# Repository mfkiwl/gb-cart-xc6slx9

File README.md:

# Various gameboy cart projects

References:
* [ESP32 DEVKIT V4 Schematic](https://dl.espressif.com/dl/schematics/esp32_devkitc_v4-sch.pdf)
* [CMOD S6 Schematic](https://reference.digilentinc.com/_media/cmod_s6:cmods6_sch.pdf)
* [ESP32 SD Card](https://github.com/espressif/arduino-esp32/tree/master/libraries/SD)
* [ESP32 PMOD](https://reference.digilentinc.com/_media/reference/pmod/pmodesp32/schematic/pmodesp32_sch.pdf)

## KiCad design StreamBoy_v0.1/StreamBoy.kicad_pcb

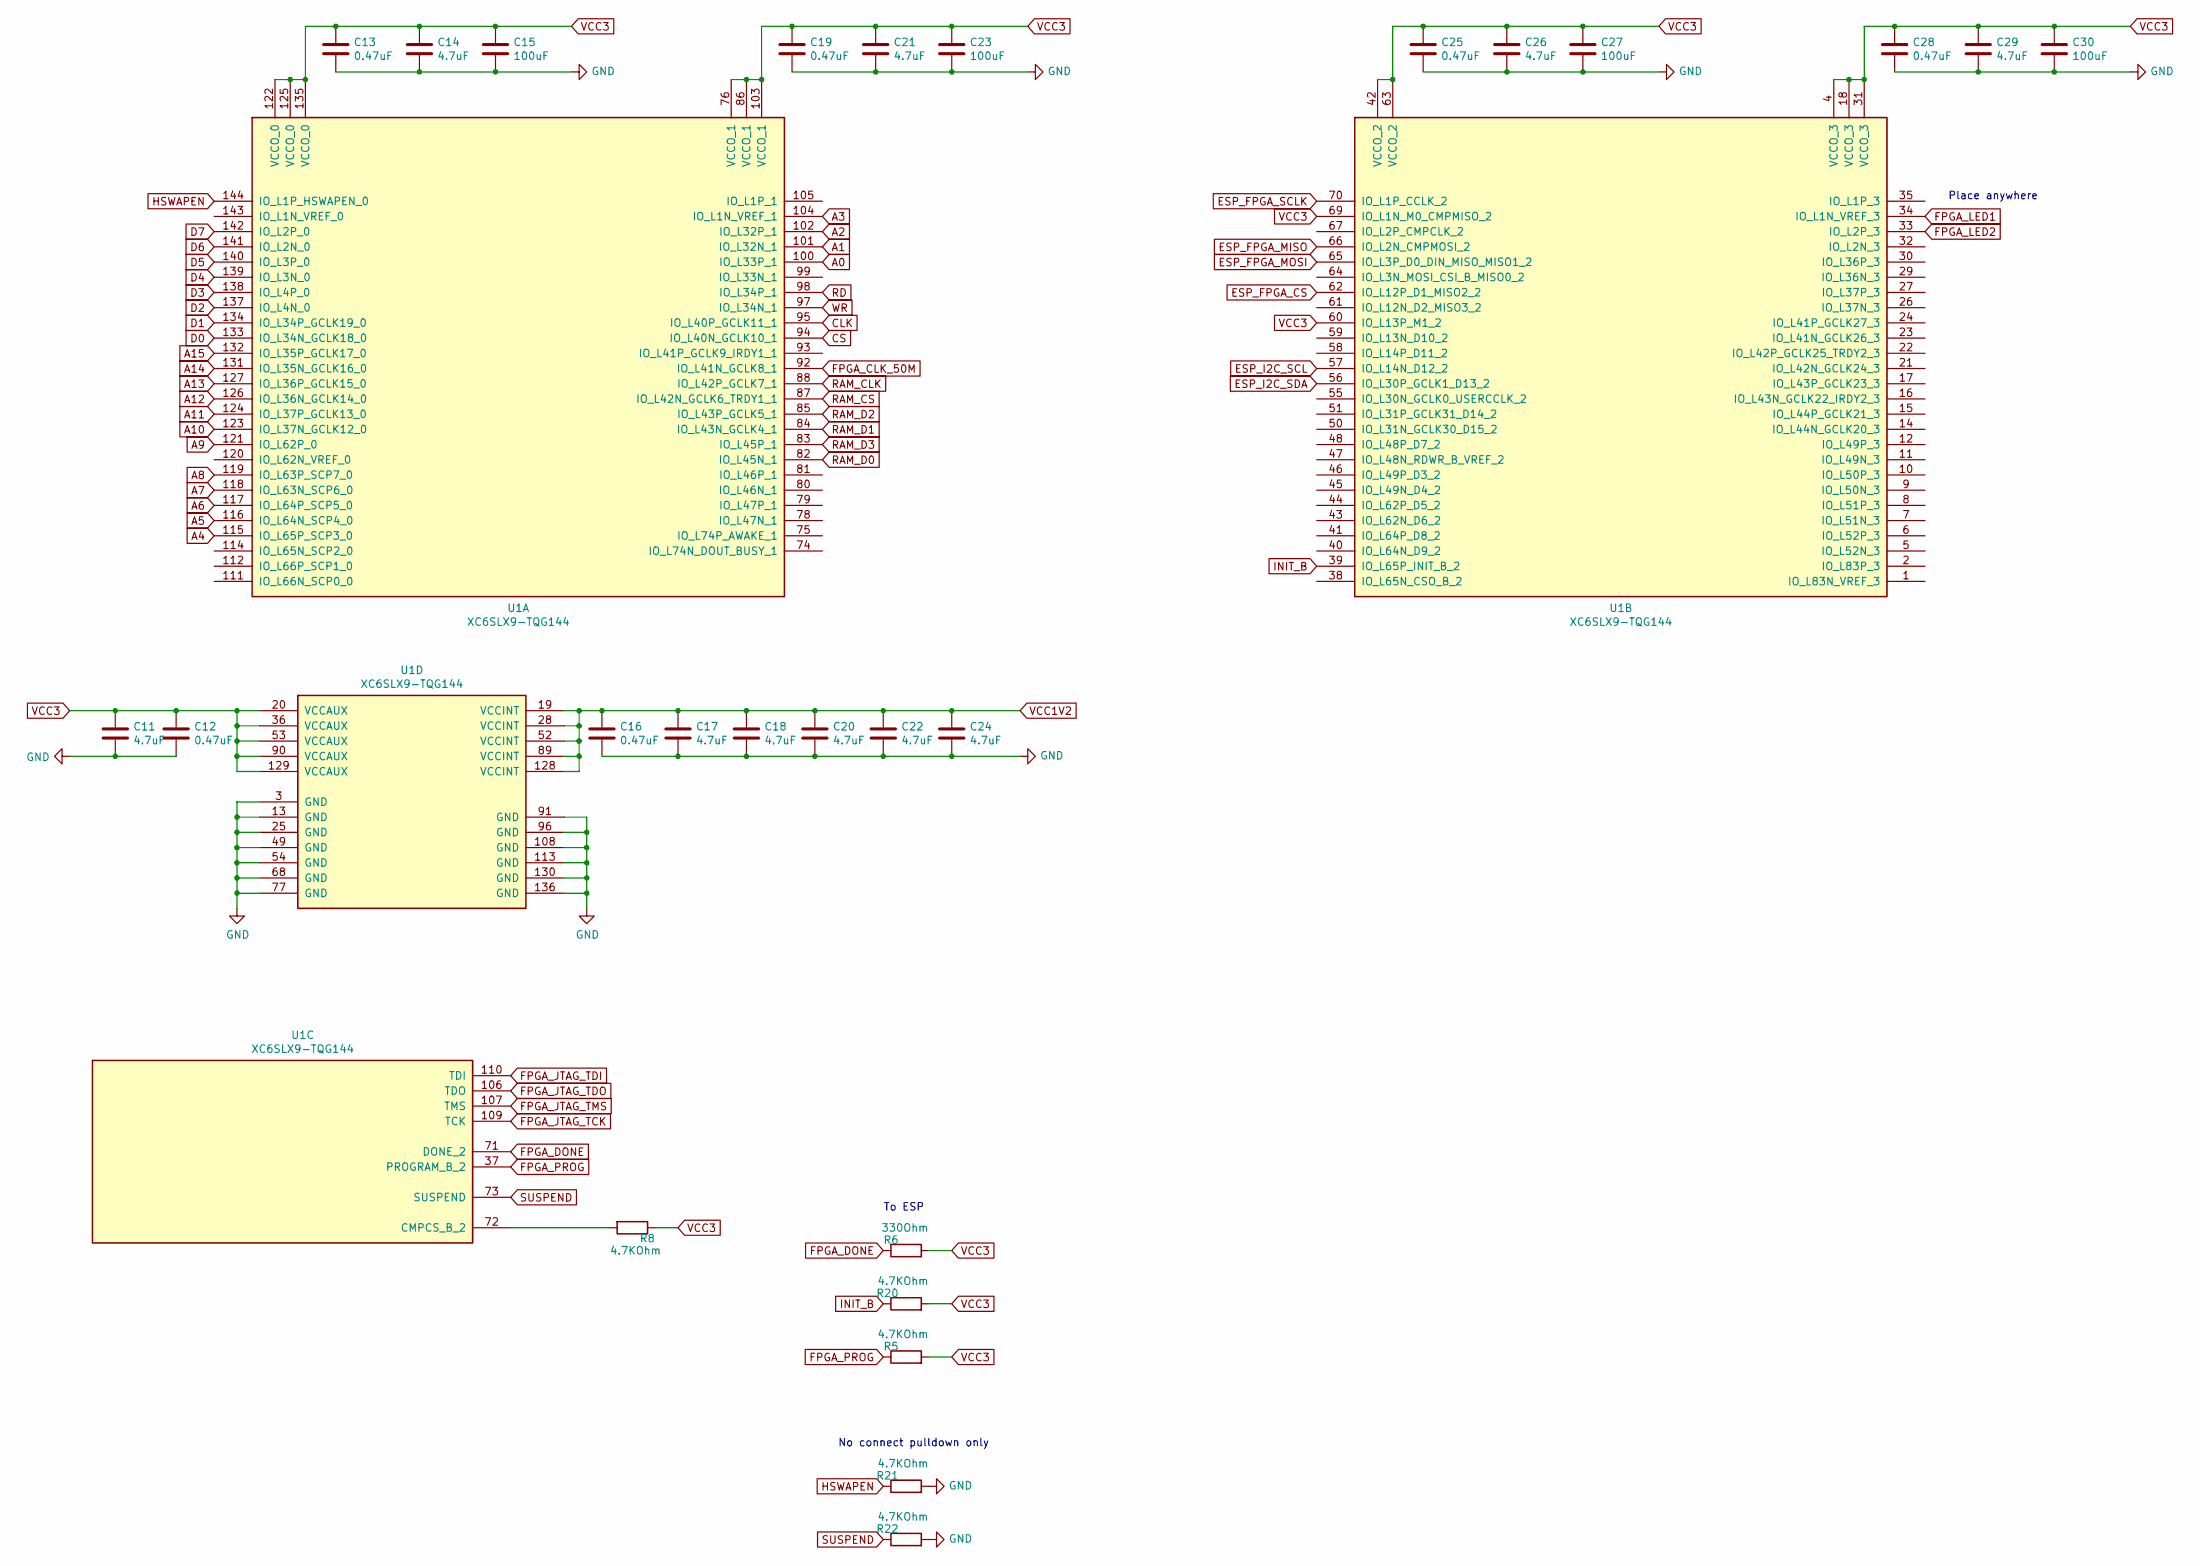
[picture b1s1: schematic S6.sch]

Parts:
C11, C14, C17, C18, C20, C21, C22, C24, C26, C29: 4.7uF; C_0402_1005Metric; lcscPartnum C23733
C12, C13, C16, C19, C25, C28: 0.47uF; C_0402_1005Metric; lcscPartnum C47339
C15, C23, C27, C30: 100uF; C_1206_3216Metric; lcscPartnum C15008
R5, R8, R20, R21, R22: 4.7KOhm; R_0402_1005Metric; lcscPartnum C25900
R6: 330Ohm; R_0402_1005Metric; lcscPartnum C25890
U1: XC6SLX9-TQG144; TQFP-144_20x20mm_P0.5mm

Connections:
A0: U1.100 (IO_L33P_1); also elsewhere on the board
A1: U1.101 (IO_L32N_1); also elsewhere on the board
A2: U1.102 (IO_L32P_1); also elsewhere on the board
A3: U1.104 (IO_L1N_VREF_1); also elsewhere on the board
A4: U1.115 (IO_L65P_SCP3_0); also elsewhere on the board
A5: U1.116 (IO_L64N_SCP4_0); also elsewhere on the board
A6: U1.117 (IO_L64P_SCP5_0); also elsewhere on the board
A7: U1.118 (IO_L63N_SCP6_0); also elsewhere on the board
A8: U1.119 (IO_L63P_SCP7_0); also elsewhere on the board
A9: U1.121 (IO_L62P_0); also elsewhere on the board
A10: U1.123 (IO_L37N_GCLK12_0); also elsewhere on the board
A11: U1.124 (IO_L37P_GCLK13_0); also elsewhere on the board
A12: U1.126 (IO_L36N_GCLK14_0); also elsewhere on the board
A13: U1.127 (IO_L36P_GCLK15_0); also elsewhere on the board
A14: U1.131 (IO_L35N_GCLK16_0); also elsewhere on the board
A15: U1.132 (IO_L35P_GCLK17_0); also elsewhere on the board
CLK: U1.95 (IO_L40P_GCLK11_1); also elsewhere on the board
CS: U1.94 (IO_L40N_GCLK10_1); also elsewhere on the board
D0: U1.133 (IO_L34N_GCLK18_0); also elsewhere on the board
D1: U1.134 (IO_L34P_GCLK19_0); also elsewhere on the board
D2: U1.137 (IO_L4N_0); also elsewhere on the board
D3: U1.138 (IO_L4P_0); also elsewhere on the board
D4: U1.139 (IO_L3N_0); also elsewhere on the board
D5: U1.140 (IO_L3P_0); also elsewhere on the board
D6: U1.141 (IO_L2N_0); also elsewhere on the board
D7: U1.142 (IO_L2P_0); also elsewhere on the board
ESP_FPGA_CS: U1.62 (IO_L12P_D1_MISO2_2); also elsewhere on the board
ESP_FPGA_MISO: U1.66 (IO_L2N_CMPMOSI_2); also elsewhere on the board
ESP_FPGA_MOSI: U1.65 (IO_L3P_D0_DIN_MISO_MISO1_2); also elsewhere on the board
ESP_FPGA_SCLK: U1.70 (IO_L1P_CCLK_2); also elsewhere on the board
ESP_I2C_SCL: U1.57 (IO_L14N_D12_2); also elsewhere on the board
ESP_I2C_SDA: U1.56 (IO_L30P_GCLK1_D13_2); also elsewhere on the board
FPGA_CLK_50M: U1.92 (IO_L41N_GCLK8_1); also elsewhere on the board
FPGA_DONE: R6.1, U1.71 (DONE_2)
FPGA_JTAG_TCK: U1.109 (TCK)
FPGA_JTAG_TDI: U1.110 (TDI)
FPGA_JTAG_TDO: U1.106 (TDO)
FPGA_JTAG_TMS: U1.107 (TMS)
FPGA_LED1: U1.34 (IO_L1N_VREF_3); also elsewhere on the board
FPGA_LED2: U1.33 (IO_L2P_3); also elsewhere on the board
FPGA_PROG: R5.1, U1.37 (PROGRAM_B_2)
GND: C11.2, C12.2, C13.2, C14.2, C15.2, C16.2, C17.2, C18.2, C19.2, C20.2, C21.2, C22.2, C23.2, C24.2, C25.2, C26.2, C27.2, C28.2, C29.2, C30.2, R21.2, R22.2, U1.3 (GND), U1.13 (GND), U1.25 (GND), U1.49 (GND), U1.54 (GND), U1.68 (GND), U1.77 (GND), U1.91 (GND), U1.96 (GND), U1.108 (GND), U1.113 (GND), U1.130 (GND), U1.136 (GND); also elsewhere on the board
HSWAPEN: R21.1, U1.144 (IO_L1P_HSWAPEN_0)
INIT_B: R20.1, U1.39 (IO_L65P_INIT_B_2)
unnamed: R8.2, U1.72 (CMPCS_B_2)
RAM_CLK: U1.88 (IO_L42P_GCLK7_1); also elsewhere on the board
RAM_CS: U1.87 (IO_L42N_GCLK6_TRDY1_1); also elsewhere on the board
RAM_D0: U1.82 (IO_L45N_1); also elsewhere on the board
RAM_D1: U1.84 (IO_L43N_GCLK4_1); also elsewhere on the board
RAM_D2: U1.85 (IO_L43P_GCLK5_1); also elsewhere on the board
RAM_D3: U1.83 (IO_L45P_1); also elsewhere on the board
RD: U1.98 (IO_L34P_1); also elsewhere on the board
SUSPEND: R22.1, U1.73 (SUSPEND)
VCC1V2: C16.1, C17.1, C18.1, C20.1, C22.1, C24.1, U1.19 (VCCINT), U1.28 (VCCINT), U1.52 (VCCINT), U1.89 (VCCINT), U1.128 (VCCINT); also elsewhere on the board
VCC3: C11.1, C12.1, C13.1, C14.1, C15.1, C19.1, C21.1, C23.1, C25.1, C26.1, C27.1, C28.1, C29.1, C30.1, R5.2, R6.2, R8.1, R20.2, U1.4 (VCCO_3), U1.18 (VCCO_3), U1.20 (VCCAUX), U1.31 (VCCO_3), U1.36 (VCCAUX), U1.42 (VCCO_2), U1.53 (VCCAUX), U1.60 (IO_L13P_M1_2), U1.63 (VCCO_2), U1.69 (IO_L1N_M0_CMPMISO_2), U1.76 (VCCO_1), U1.86 (VCCO_1), U1.90 (VCCAUX), U1.103 (VCCO_1), U1.122 (VCCO_0), U1.125 (VCCO_0), U1.129 (VCCAUX), U1.135 (VCCO_0); also elsewhere on the board
WR: U1.97 (IO_L34N_1); also elsewhere on the board

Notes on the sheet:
Place anywhere
To ESP
No connect pulldown only

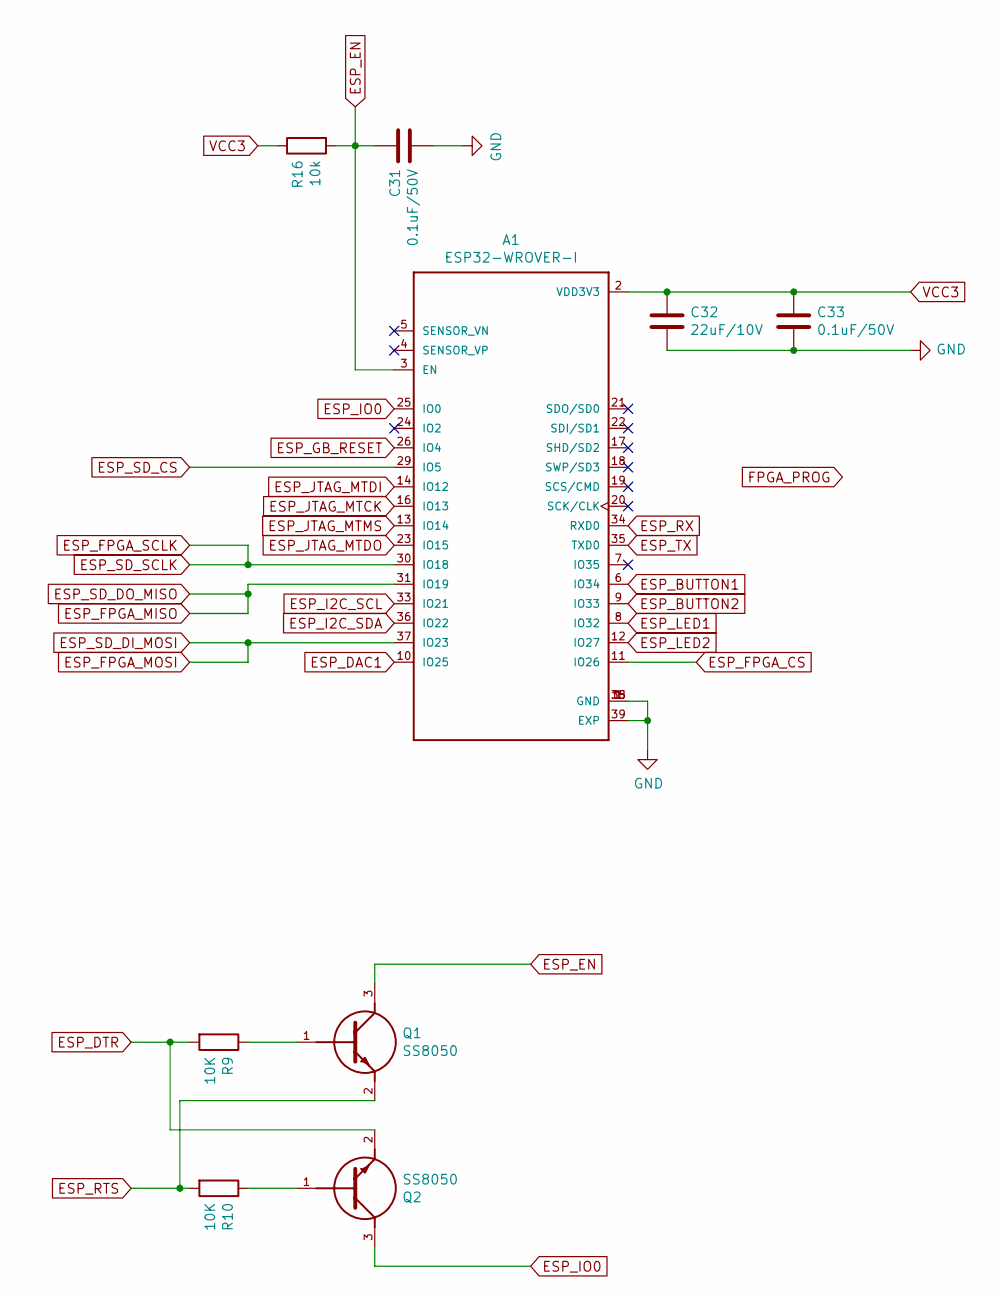
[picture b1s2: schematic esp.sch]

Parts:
A1: ESP32-WROVER-I; XCVR_ESP32-WROVER-I
C31, C33: 0.1uF/50V; C_0805_2012Metric; lcscPartnum C15195
C32: 22uF/10V; C_0805_2012Metric
Q1, Q2: SS8050; SOT95P240X115-3N; lcscPartnum C2146
R9, R10: 10K; R_0805_2012Metric
R16: 10k; R_0805_2012Metric

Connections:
ESP_BUTTON1: A1.6 (IO34); also elsewhere on the board
ESP_BUTTON2: A1.9 (IO33); also elsewhere on the board
ESP_DAC1: A1.10 (IO25); also elsewhere on the board
ESP_DTR: Q2.2 (E), R9.2; also elsewhere on the board
ESP_EN: A1.3 (EN), C31.1, Q1.3 (C), R16.2
ESP_FPGA_CS: A1.11 (IO26); also elsewhere on the board
ESP_FPGA_MISO: A1.31 (IO19); also elsewhere on the board
ESP_FPGA_MOSI: A1.37 (IO23); also elsewhere on the board
ESP_FPGA_SCLK: A1.30 (IO18); also elsewhere on the board
ESP_I2C_SCL: A1.33 (IO21); also elsewhere on the board
ESP_I2C_SDA: A1.36 (IO22); also elsewhere on the board
ESP_IO0: A1.25 (IO0), Q2.3 (C)
ESP_JTAG_MTCK: A1.16 (IO13); also elsewhere on the board
ESP_JTAG_MTDI: A1.14 (IO12); also elsewhere on the board
ESP_JTAG_MTDO: A1.23 (IO15); also elsewhere on the board
ESP_JTAG_MTMS: A1.13 (IO14); also elsewhere on the board
ESP_LED1: A1.8 (IO32); also elsewhere on the board
ESP_LED2: A1.12 (IO27); also elsewhere on the board
ESP_RTS: Q1.2 (E), R10.2; also elsewhere on the board
ESP_RX: A1.34 (RXD0); also elsewhere on the board
ESP_SD_CS: A1.29 (IO5); also elsewhere on the board
ESP_TX: A1.35 (TXD0); also elsewhere on the board
GND: A1.1 (GND), A1.15 (GND), A1.38 (GND), A1.39 (EXP), C31.2, C32.2, C33.2; also elsewhere on the board
unnamed: Q1.1 (B), R9.1
unnamed: Q2.1 (B), R10.1
VCC3: A1.2 (VDD3V3), C32.1, C33.1, R16.1; also elsewhere on the board

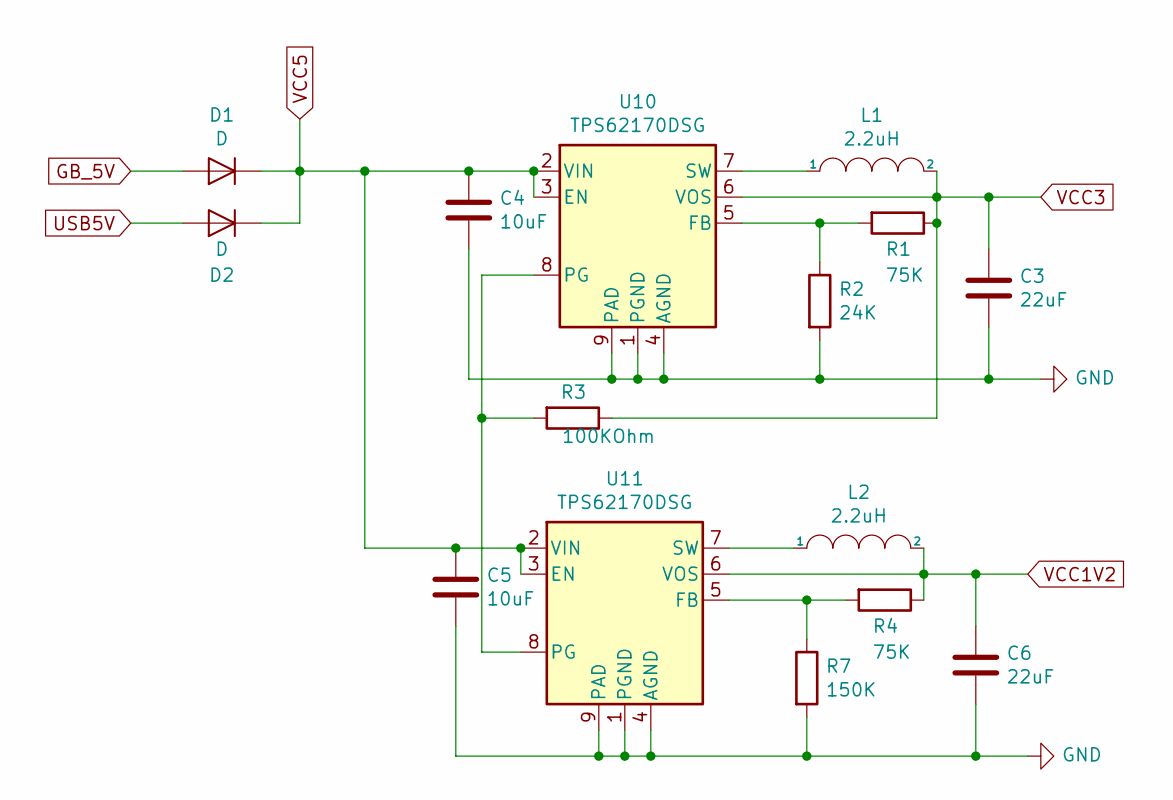
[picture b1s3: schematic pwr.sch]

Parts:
C3, C6: 22uF; C_0603_1608Metric; lcscPartnum C59461
C4, C5: 10uF; C_0402_1005Metric; lcscPartnum C15525
D1, D2: D; D_SOD-123F; lcscPartnum C64898
L1, L2: 2.2uH; L_0805_2012Metric; lcscPartnum C1043
R1, R4: 75K; R_0402_1005Metric; lcscPartnum C25798
R2: 24K; R_0402_1005Metric; lcscPartnum C25769
R3: 100KOhm; R_0402_1005Metric; lcscPartnum C25741
R7: 150K; R_0402_1005Metric; lcscPartnum C25755
U10, U11: TPS62170DSG; WSON-8-1EP_2x2mm_P0.5mm_EP0.9x1.6mm_ThermalVias

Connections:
GB_5V: D1.2 (A); also elsewhere on the board
GND: C3.2, C4.2, C5.2, C6.2, R2.2, R7.2, U10.1 (PGND), U10.4 (AGND), U10.9 (PAD), U11.1 (PGND), U11.4 (AGND), U11.9 (PAD); also elsewhere on the board
unnamed: L1.1, U10.7 (SW)
unnamed: L2.1, U11.7 (SW)
unnamed: R1.2, R2.1, U10.5 (FB)
unnamed: R3.2, U10.8 (PG), U11.8 (PG)
unnamed: R4.2, R7.1, U11.5 (FB)
USB5V: D2.2 (A); also elsewhere on the board
VCC1V2: C6.1, L2.2, R4.1, U11.6 (VOS); also elsewhere on the board
VCC3: C3.1, L1.2, R1.1, R3.1, U10.6 (VOS); also elsewhere on the board
VCC5: C4.1, C5.1, D1.1 (K), D2.1 (K), U10.2 (VIN), U10.3 (EN), U11.2 (VIN), U11.3 (EN); also elsewhere on the board

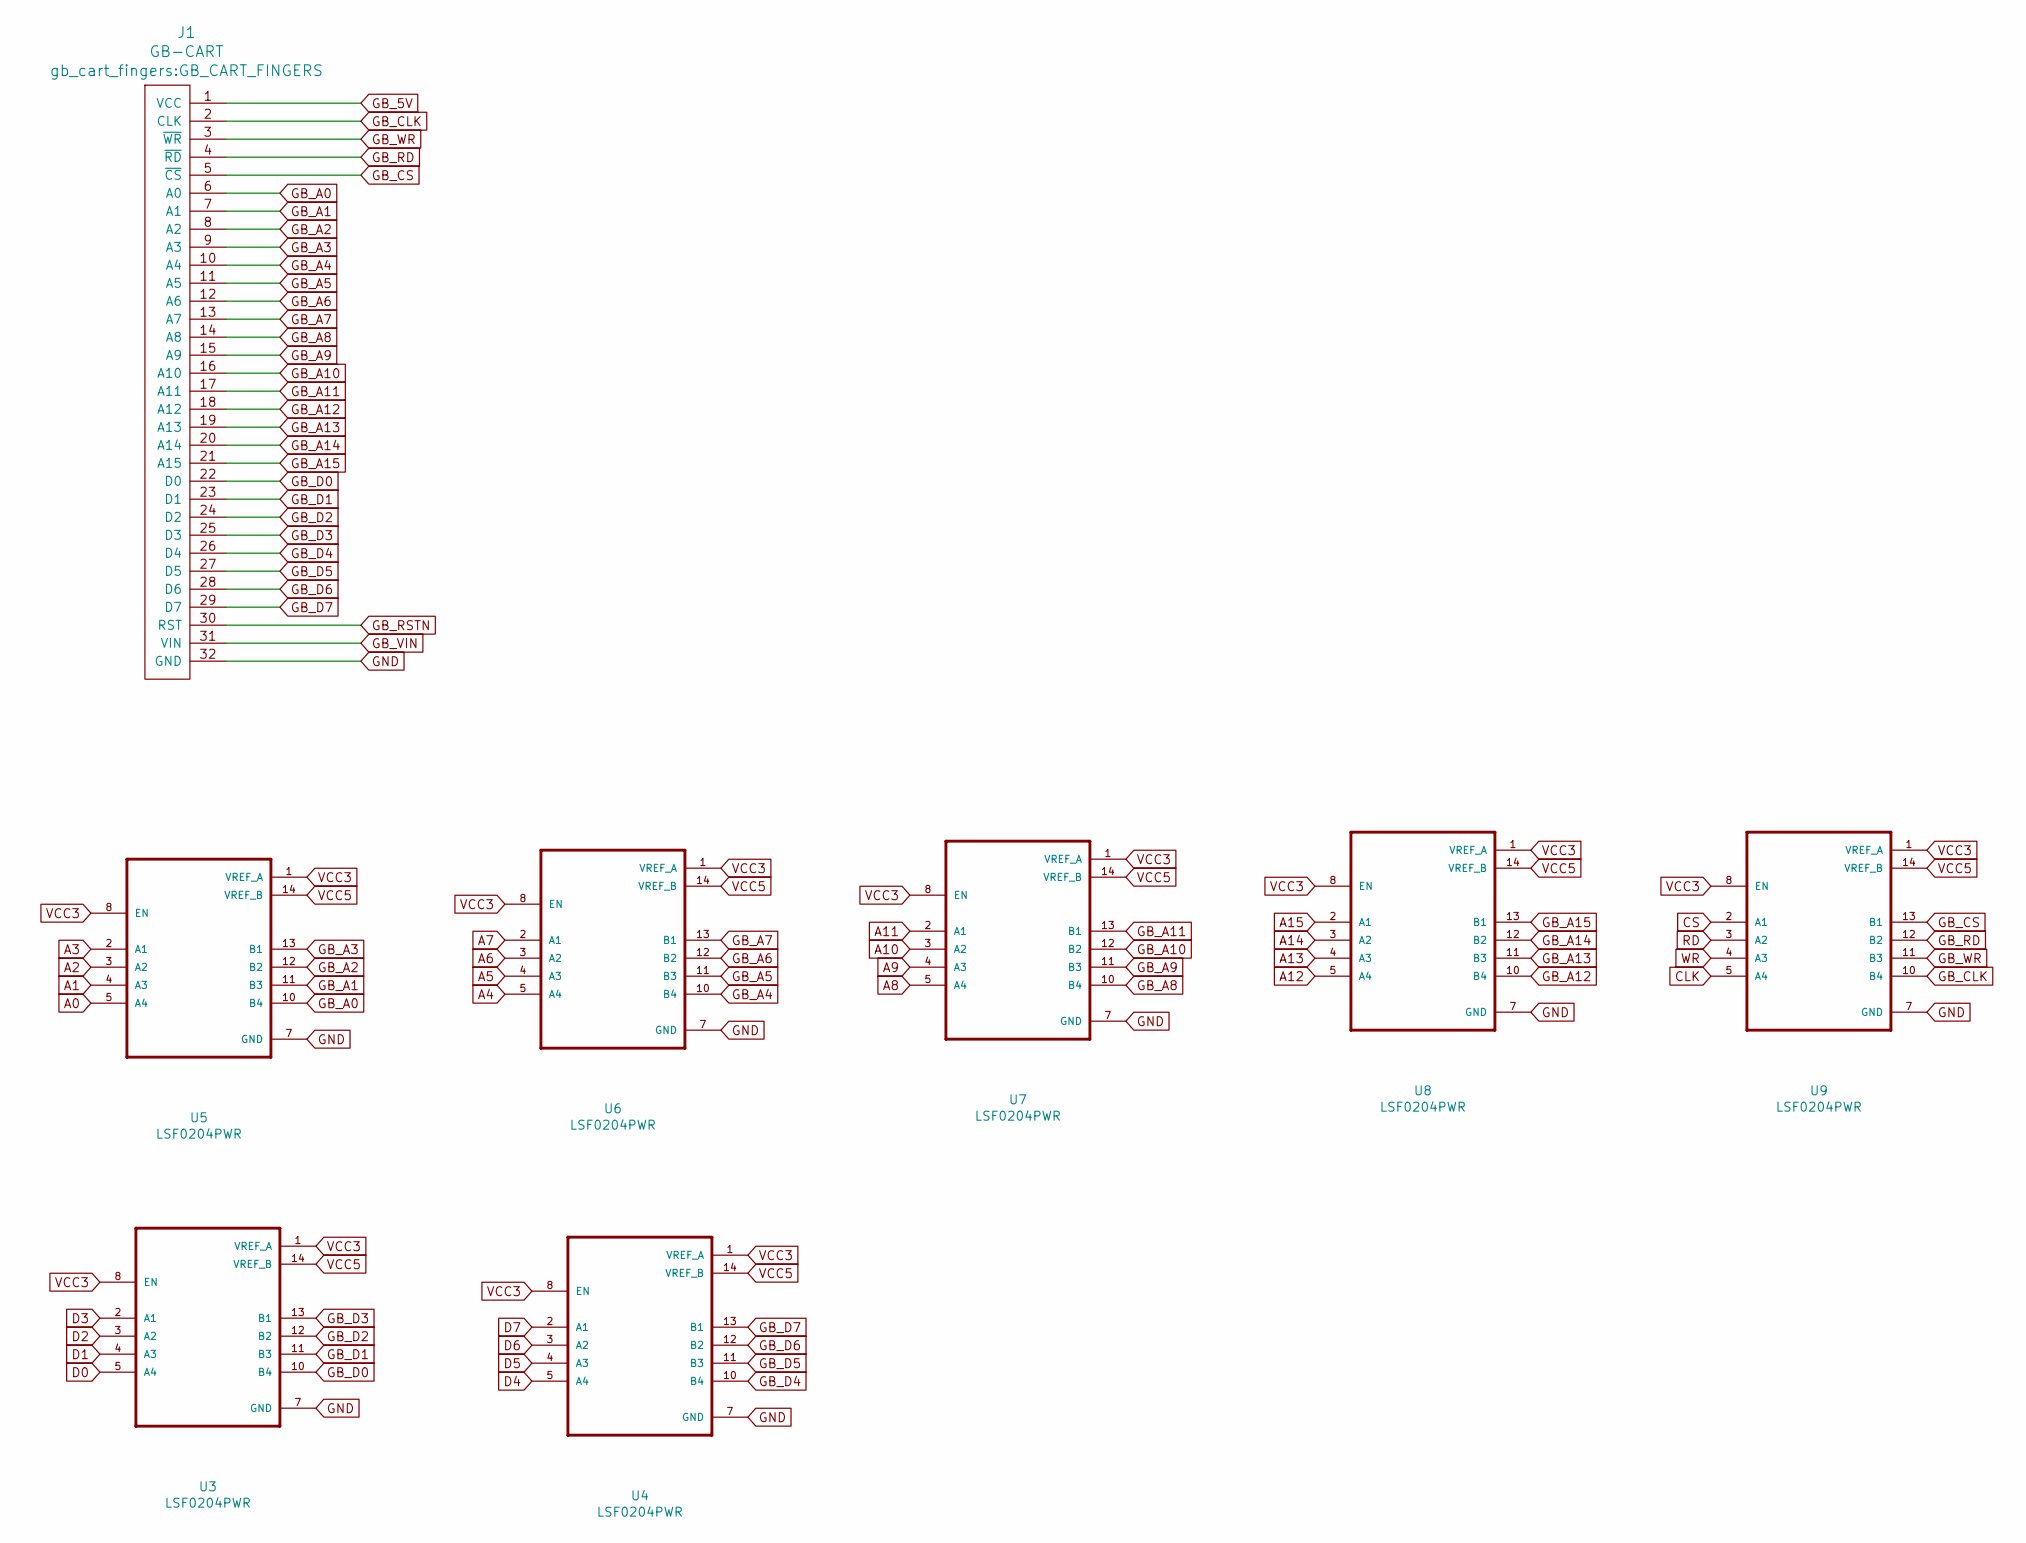
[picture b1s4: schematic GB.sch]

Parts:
J1: GB-CART; GB_CART_FINGERS
U3, U4, U5, U6, U7, U8, U9: LSF0204PWR; SOP65P640X120-14N

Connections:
A0: U5.5 (A4); also elsewhere on the board
A1: U5.4 (A3); also elsewhere on the board
A2: U5.3 (A2); also elsewhere on the board
A3: U5.2 (A1); also elsewhere on the board
A4: U6.5 (A4); also elsewhere on the board
A5: U6.4 (A3); also elsewhere on the board
A6: U6.3 (A2); also elsewhere on the board
A7: U6.2 (A1); also elsewhere on the board
A8: U7.5 (A4); also elsewhere on the board
A9: U7.4 (A3); also elsewhere on the board
A10: U7.3 (A2); also elsewhere on the board
A11: U7.2 (A1); also elsewhere on the board
A12: U8.5 (A4); also elsewhere on the board
A13: U8.4 (A3); also elsewhere on the board
A14: U8.3 (A2); also elsewhere on the board
A15: U8.2 (A1); also elsewhere on the board
CLK: U9.5 (A4); also elsewhere on the board
CS: U9.2 (A1); also elsewhere on the board
D0: U3.5 (A4); also elsewhere on the board
D1: U3.4 (A3); also elsewhere on the board
D2: U3.3 (A2); also elsewhere on the board
D3: U3.2 (A1); also elsewhere on the board
D4: U4.5 (A4); also elsewhere on the board
D5: U4.4 (A3); also elsewhere on the board
D6: U4.3 (A2); also elsewhere on the board
D7: U4.2 (A1); also elsewhere on the board
ESP_DAC1: J1.31 (VIN); also elsewhere on the board
GB_5V: J1.1 (VCC); also elsewhere on the board
GB_A0: J1.6 (A0), U5.10 (B4)
GB_A1: J1.7 (A1), U5.11 (B3)
GB_A2: J1.8 (A2), U5.12 (B2)
GB_A3: J1.9 (A3), U5.13 (B1)
GB_A4: J1.10 (A4), U6.10 (B4)
GB_A5: J1.11 (A5), U6.11 (B3)
GB_A6: J1.12 (A6), U6.12 (B2)
GB_A7: J1.13 (A7), U6.13 (B1)
GB_A8: J1.14 (A8), U7.10 (B4)
GB_A9: J1.15 (A9), U7.11 (B3)
GB_A10: J1.16 (A10), U7.12 (B2)
GB_A11: J1.17 (A11), U7.13 (B1)
GB_A12: J1.18 (A12), U8.10 (B4)
GB_A13: J1.19 (A13), U8.11 (B3)
GB_A14: J1.20 (A14), U8.12 (B2)
GB_A15: J1.21 (A15), U8.13 (B1)
GB_CLK: J1.2 (CLK), U9.10 (B4)
GB_CS: J1.5 (~CS), U9.13 (B1)
GB_D0: J1.22 (D0), U3.10 (B4)
GB_D1: J1.23 (D1), U3.11 (B3)
GB_D2: J1.24 (D2), U3.12 (B2)
GB_D3: J1.25 (D3), U3.13 (B1)
GB_D4: J1.26 (D4), U4.10 (B4)
GB_D5: J1.27 (D5), U4.11 (B3)
GB_D6: J1.28 (D6), U4.12 (B2)
GB_D7: J1.29 (D7), U4.13 (B1)
GB_RD: J1.4 (~RD), U9.12 (B2)
GB_WR: J1.3 (~WR), U9.11 (B3)
GND: J1.32 (GND), U3.7 (GND), U4.7 (GND), U5.7 (GND), U6.7 (GND), U7.7 (GND), U8.7 (GND), U9.7 (GND); also elsewhere on the board
RD: U9.3 (A2); also elsewhere on the board
VCC3: U3.1 (VREF_A), U3.8 (EN), U4.1 (VREF_A), U4.8 (EN), U5.1 (VREF_A), U5.8 (EN), U6.1 (VREF_A), U6.8 (EN), U7.1 (VREF_A), U7.8 (EN), U8.1 (VREF_A), U8.8 (EN), U9.1 (VREF_A), U9.8 (EN); also elsewhere on the board
VCC5: U3.14 (VREF_B), U4.14 (VREF_B), U5.14 (VREF_B), U6.14 (VREF_B), U7.14 (VREF_B), U8.14 (VREF_B), U9.14 (VREF_B); also elsewhere on the board
WR: U9.4 (A3); also elsewhere on the board

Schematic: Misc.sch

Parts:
C1: 0.1uF; C_0402_1005Metric
C2: 15pF; C_0402_1005Metric
C7: 1uF; C_0805_2012Metric
C8, C10: 0.1uF; C_0805_2012Metric
C9: 4.7uF; C_0402_1005Metric; lcscPartnum C23733
IC1: LY68L6400SLIT; SOIC127P600X175-8N; Manufacturer_Part_Number LY68L6400SLIT
JUSB1: USB_B_Micro; USB_Micro-B_Molex_47346-0001
R11: 2K; R_0805_2012Metric
R12: 10K; R_0805_2012Metric
U12: CP2102N-A01-GQFN28; QFN-28-1EP_5x5mm_P0.5mm_EP3.35x3.35mm
X1: SG-7050CBN; Oscillator_SMD_SeikoEpson_SG8002CA-4Pin_7.0x5.0mm

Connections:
ESP_DTR: U12.28; also elsewhere on the board
ESP_RTS: U12.24; also elsewhere on the board
ESP_RX: U12.26; also elsewhere on the board
ESP_TX: U12.25; also elsewhere on the board
FPGA_CLK_50M: C2.1, X1.3 (OUT); also elsewhere on the board
GND: C2.2, C7.2, C8.2, C9.2, C10.2, IC1.4 (VSS), JUSB1.5 (GND), JUSB1.6 (Shield), R12.2, U12.3, U12.29, X1.2 (GND); also elsewhere on the board
unnamed: C1.2, X1.1 (~ST), X1.4 (VCC)
unnamed: JUSB1.2 (D-), U12.5
unnamed: JUSB1.3 (D+), U12.4
unnamed: R11.1, U12.9
unnamed: R12.1, U12.11
RAM_CLK: IC1.6 (SCLK); also elsewhere on the board
RAM_CS: IC1.1 (CE#); also elsewhere on the board
RAM_D0: IC1.5 (SI/SIO[0]); also elsewhere on the board
RAM_D1: IC1.2 (SO/SIO[1]); also elsewhere on the board
RAM_D2: IC1.3 (SIO[2]); also elsewhere on the board
RAM_D3: IC1.7 (SIO[3]); also elsewhere on the board
USB5V: JUSB1.1 (VBUS), U12.8; also elsewhere on the board
VCC3: C1.1, C7.1, C8.1, C9.1, C10.1, IC1.8 (VCC), R11.2, U12.6, U12.7; also elsewhere on the board

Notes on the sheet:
Note, RX/TX are flipped

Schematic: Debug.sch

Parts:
D3, D4, D5, D6: LED; LED_1210_3225Metric
JDAC1: Conn_01x02; PinHeader_1x02_P2.54mm_Vertical
JFPGAI2C1: Conn_01x02; PinHeader_1x02_P2.54mm_Vertical
JFPGASPI1: Conn_01x04; PinHeader_1x04_P2.54mm_Vertical
JPOWER1V2, JPOWER3V1, JPOWER5V1: Conn_01x02; PinHeader_1x02_P2.54mm_Vertical
JRESET1: Conn_01x02; PinHeader_1x02_P2.54mm_Vertical
JSD1: Micro_SD_Card; TF015
JTAG_ESP1: Conn_01x04; PinHeader_1x04_P2.54mm_Vertical
JUART1: Conn_01x06; PinHeader_1x06_P2.54mm_Vertical
R13, R14, R15, R17, R18, R19: 4.7KOhm; R_0402_1005Metric; lcscPartnum C25900
R42: 10K; R_0805_2012Metric
SW_B1, SW_B2: SW_Push; SW_PUSH_6mm

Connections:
ESP_BUTTON1: R18.2, SW_B1.2; also elsewhere on the board
ESP_BUTTON2: R19.2, SW_B2.2; also elsewhere on the board
ESP_DAC1: JDAC1.1; also elsewhere on the board
ESP_DTR: JUART1.4; also elsewhere on the board
ESP_FPGA_CS: JFPGASPI1.4; also elsewhere on the board
ESP_FPGA_MISO: JFPGASPI1.3, JSD1.7 (DAT0); also elsewhere on the board
ESP_FPGA_MOSI: JFPGASPI1.2, JSD1.3 (CMD); also elsewhere on the board
ESP_FPGA_SCLK: JFPGASPI1.1, JSD1.5 (CLX); also elsewhere on the board
ESP_I2C_SCL: JFPGAI2C1.2; also elsewhere on the board
ESP_I2C_SDA: JFPGAI2C1.1; also elsewhere on the board
ESP_JTAG_MTCK: JTAG_ESP1.3; also elsewhere on the board
ESP_JTAG_MTDI: JTAG_ESP1.2; also elsewhere on the board
ESP_JTAG_MTDO: JTAG_ESP1.4; also elsewhere on the board
ESP_JTAG_MTMS: JTAG_ESP1.1; also elsewhere on the board
ESP_LED1: R13.1; also elsewhere on the board
ESP_LED2: R14.1; also elsewhere on the board
ESP_RTS: JUART1.5; also elsewhere on the board
ESP_RX: JUART1.3; also elsewhere on the board
ESP_SD_CS: JSD1.2 (CD/DAT3); also elsewhere on the board
ESP_TX: JUART1.2; also elsewhere on the board
FPGA_LED1: R15.1; also elsewhere on the board
FPGA_LED2: R17.1; also elsewhere on the board
GND: D3.1, D4.1, D5.1, D6.1, JDAC1.2, JPOWER1V2.2, JPOWER3V1.2, JPOWER5V1.2, JRESET1.2, JSD1.1 (DAT2), JSD1.6 (VSS), JSD1.8 (DAT1), JSD1.9 (CD), JSD1.10, JSD1.11, JSD1.12, JSD1.13, JUART1.6, R18.1, R19.1; also elsewhere on the board
unnamed: D3.2, R13.2
unnamed: D4.2, R14.2
unnamed: D5.2, R15.2
unnamed: D6.2, R17.2
VCC1V2: JPOWER1V2.1; also elsewhere on the board
VCC3: JPOWER3V1.1, JSD1.4 (VDD), JUART1.1, SW_B1.1, SW_B2.1; also elsewhere on the board
VCC5: JPOWER5V1.1, R42.2; also elsewhere on the board

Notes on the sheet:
How do we connect this?

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
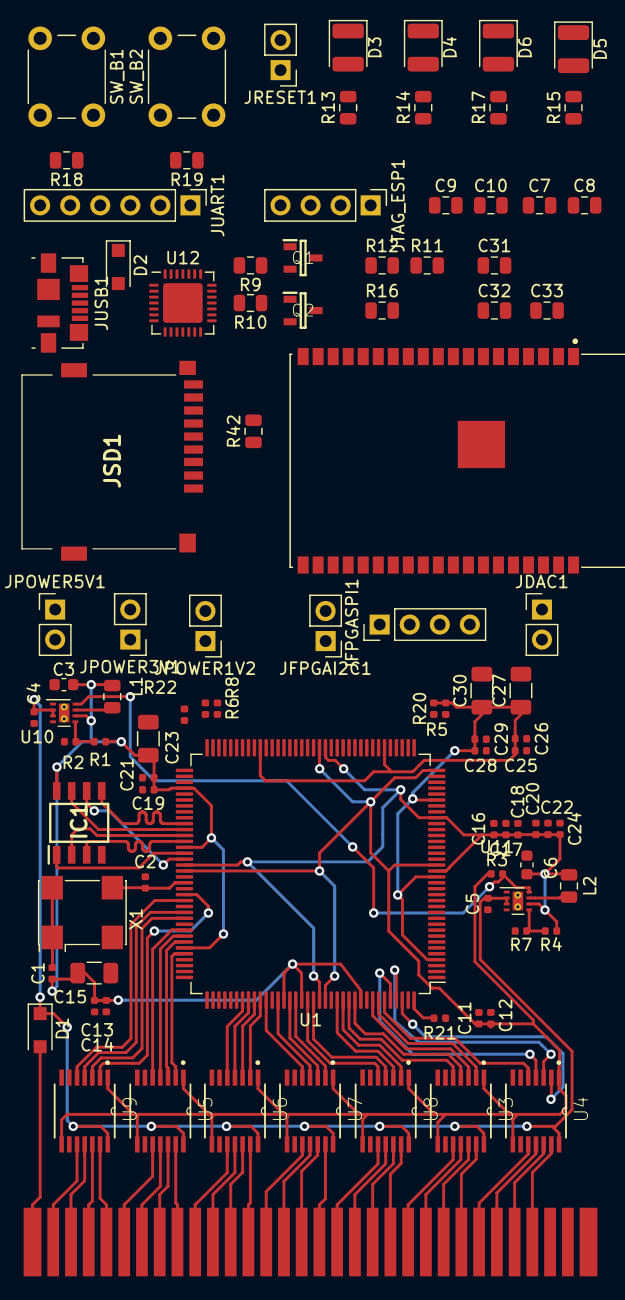
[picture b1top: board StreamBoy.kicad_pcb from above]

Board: 2 copper layers, 94 parts (0 on the bottom side), 116 nets.

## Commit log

2019-12-28 Add Libs
2019-12-28 Project Added
2019-12-28 pcb also
2019-12-28 ignore
2019-12-28 add usb
2019-12-28 Bunch of stuff
2019-12-29 Power to the masses
2019-12-29 Add ESP32-WROVER-I
2019-12-29 Add refs to README
2019-12-29 Temp
2019-12-30 Add esp pins
2019-12-30 Add esp pins to fpga
2019-12-30 Add more debug pins
2019-12-30 Add SD Card to debug
2019-12-30 Fix one resistor in pwr
2019-12-30 Connect uart
2019-12-30 Flip RX/TX, Move esp prog. circuit
2019-12-30 Connect RAM temporarily
2019-12-30 Update some labels
2019-12-30 Add leds and buttons to debug
2019-12-30 More renumbering
2019-12-30 Brute force stuff onto a pcb
2019-12-30 Replace reset button with a jumper
2020-01-03 Added most stuff to fpga
2020-01-04 I hate component placement!
2020-01-04 Started to route some stuff
2020-01-04 GB Reset fixed and moved some stuff
